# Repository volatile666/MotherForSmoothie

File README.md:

# MotherForSmoothie

#####DEVELOPMENT IN PROGRESS! UNTESTED!

Motherboad for LPCxpresso1769 and Pololu DRV8825 or compatible for running the awesome smoothieware. If you do have a spare LPCxpresso (maybe from a smoothie on breadboard experiment?) and dont need all of smoothieboards features this is for you.

#####Feature differences with smoothie

-80*100mm, 2 layers

-up to 4 stepper driver modules onboad, connector for 1 additional external driver

-no digital current adjustment (pot on the stepper modules instead)

-micro USB instead of USB-B

-1 big mosfet (heated bed?)

-1 small mosfet (extruder?)

-1 small mosfet connected to 12V (fan?)

-ATX connector for power supply, no internal regulators

-fan monitoring (for a critical fan)

-flowmeter connector with monitoring (laser cooling pump?)

#####What needs to be done?

-double check the things not in red boxes

-produce a prototype!

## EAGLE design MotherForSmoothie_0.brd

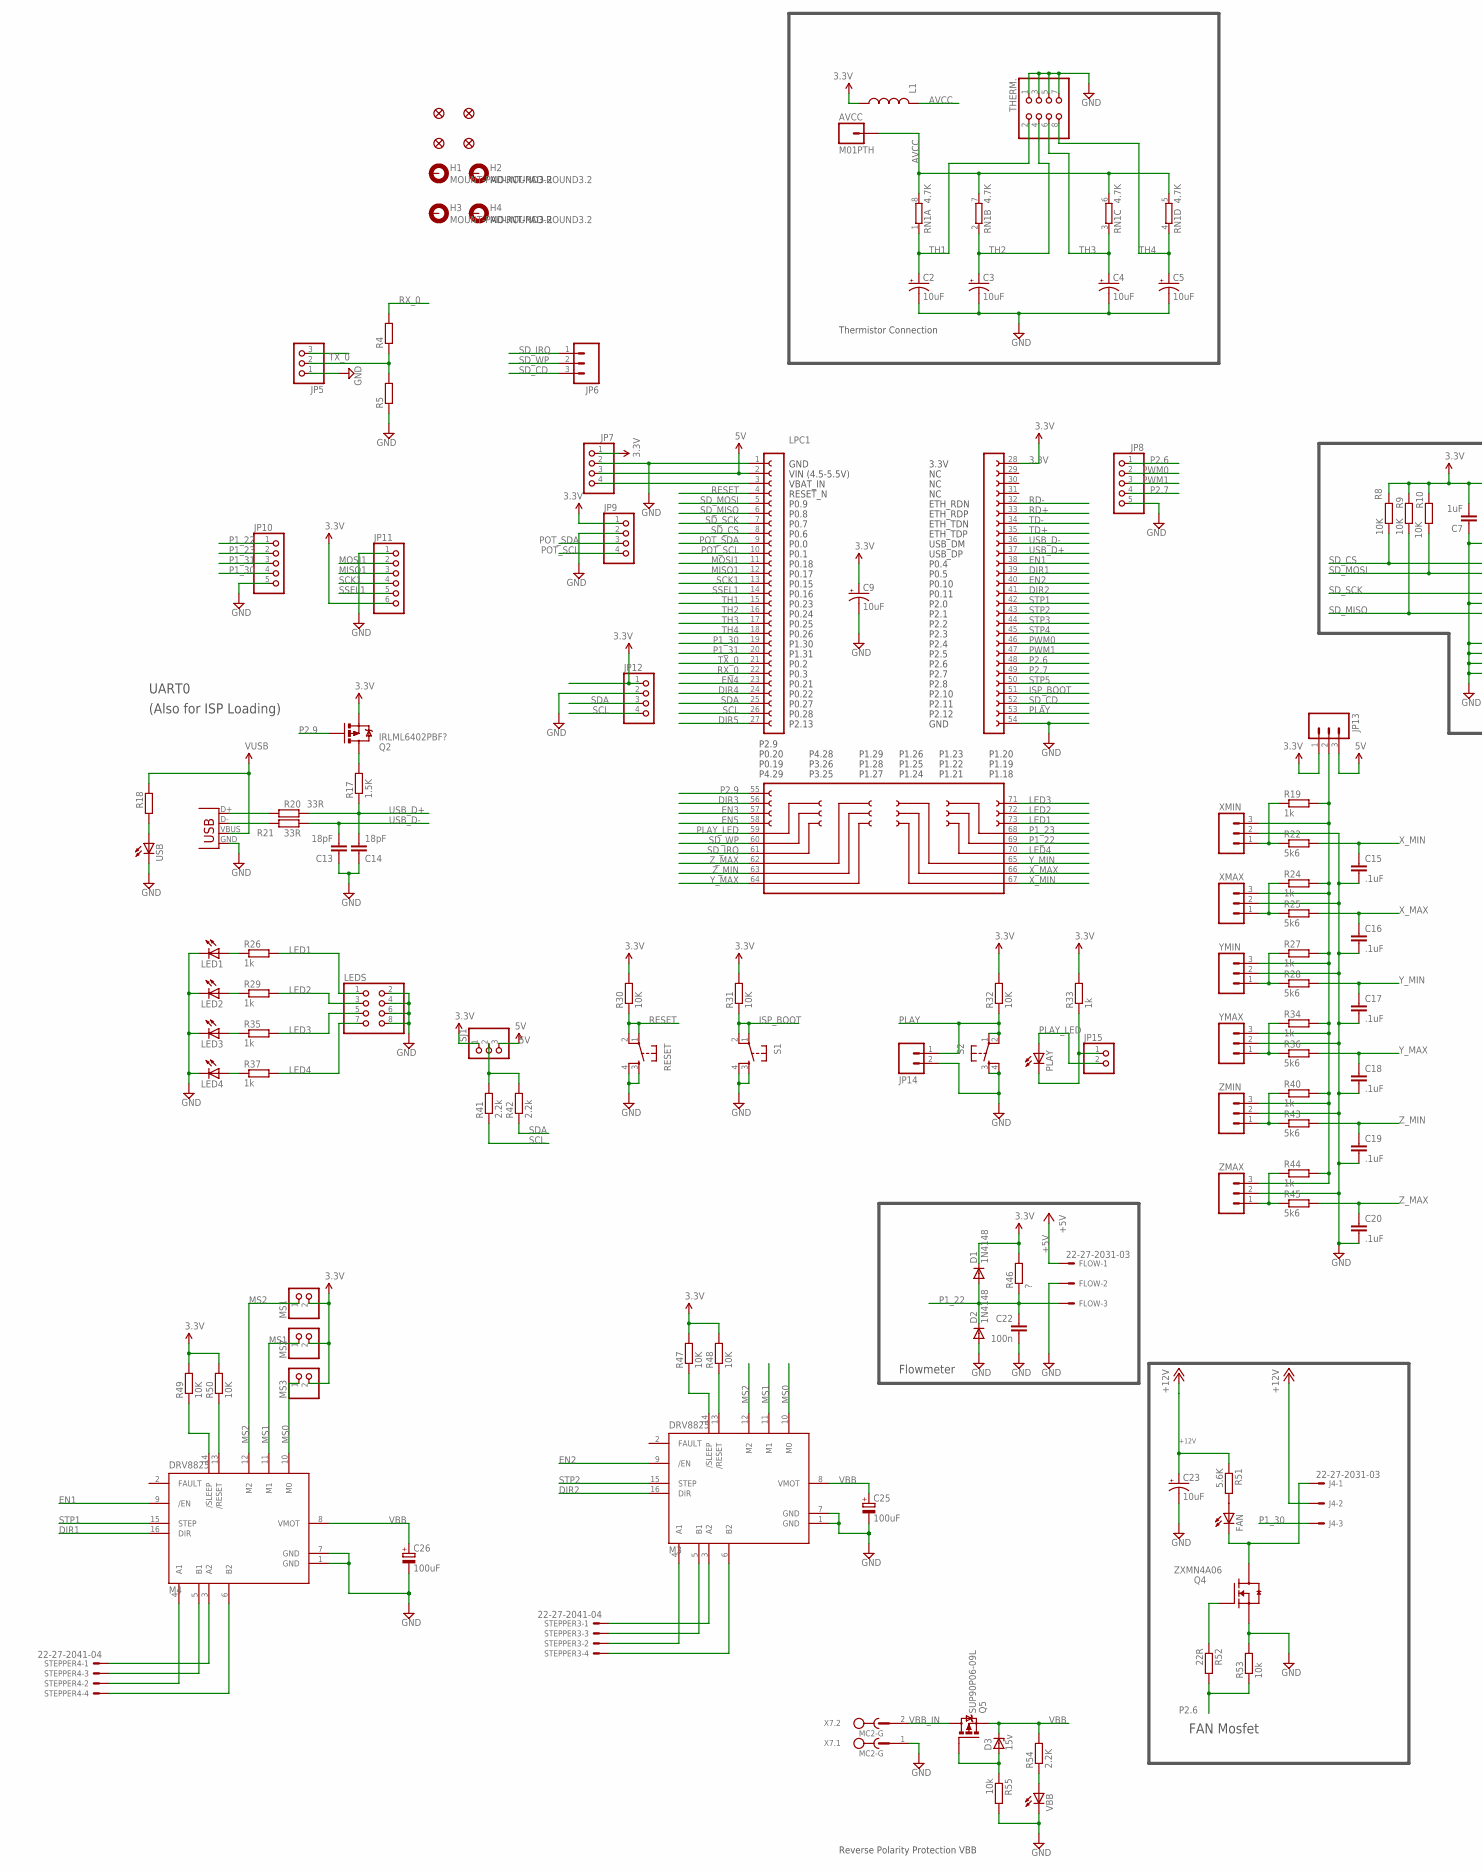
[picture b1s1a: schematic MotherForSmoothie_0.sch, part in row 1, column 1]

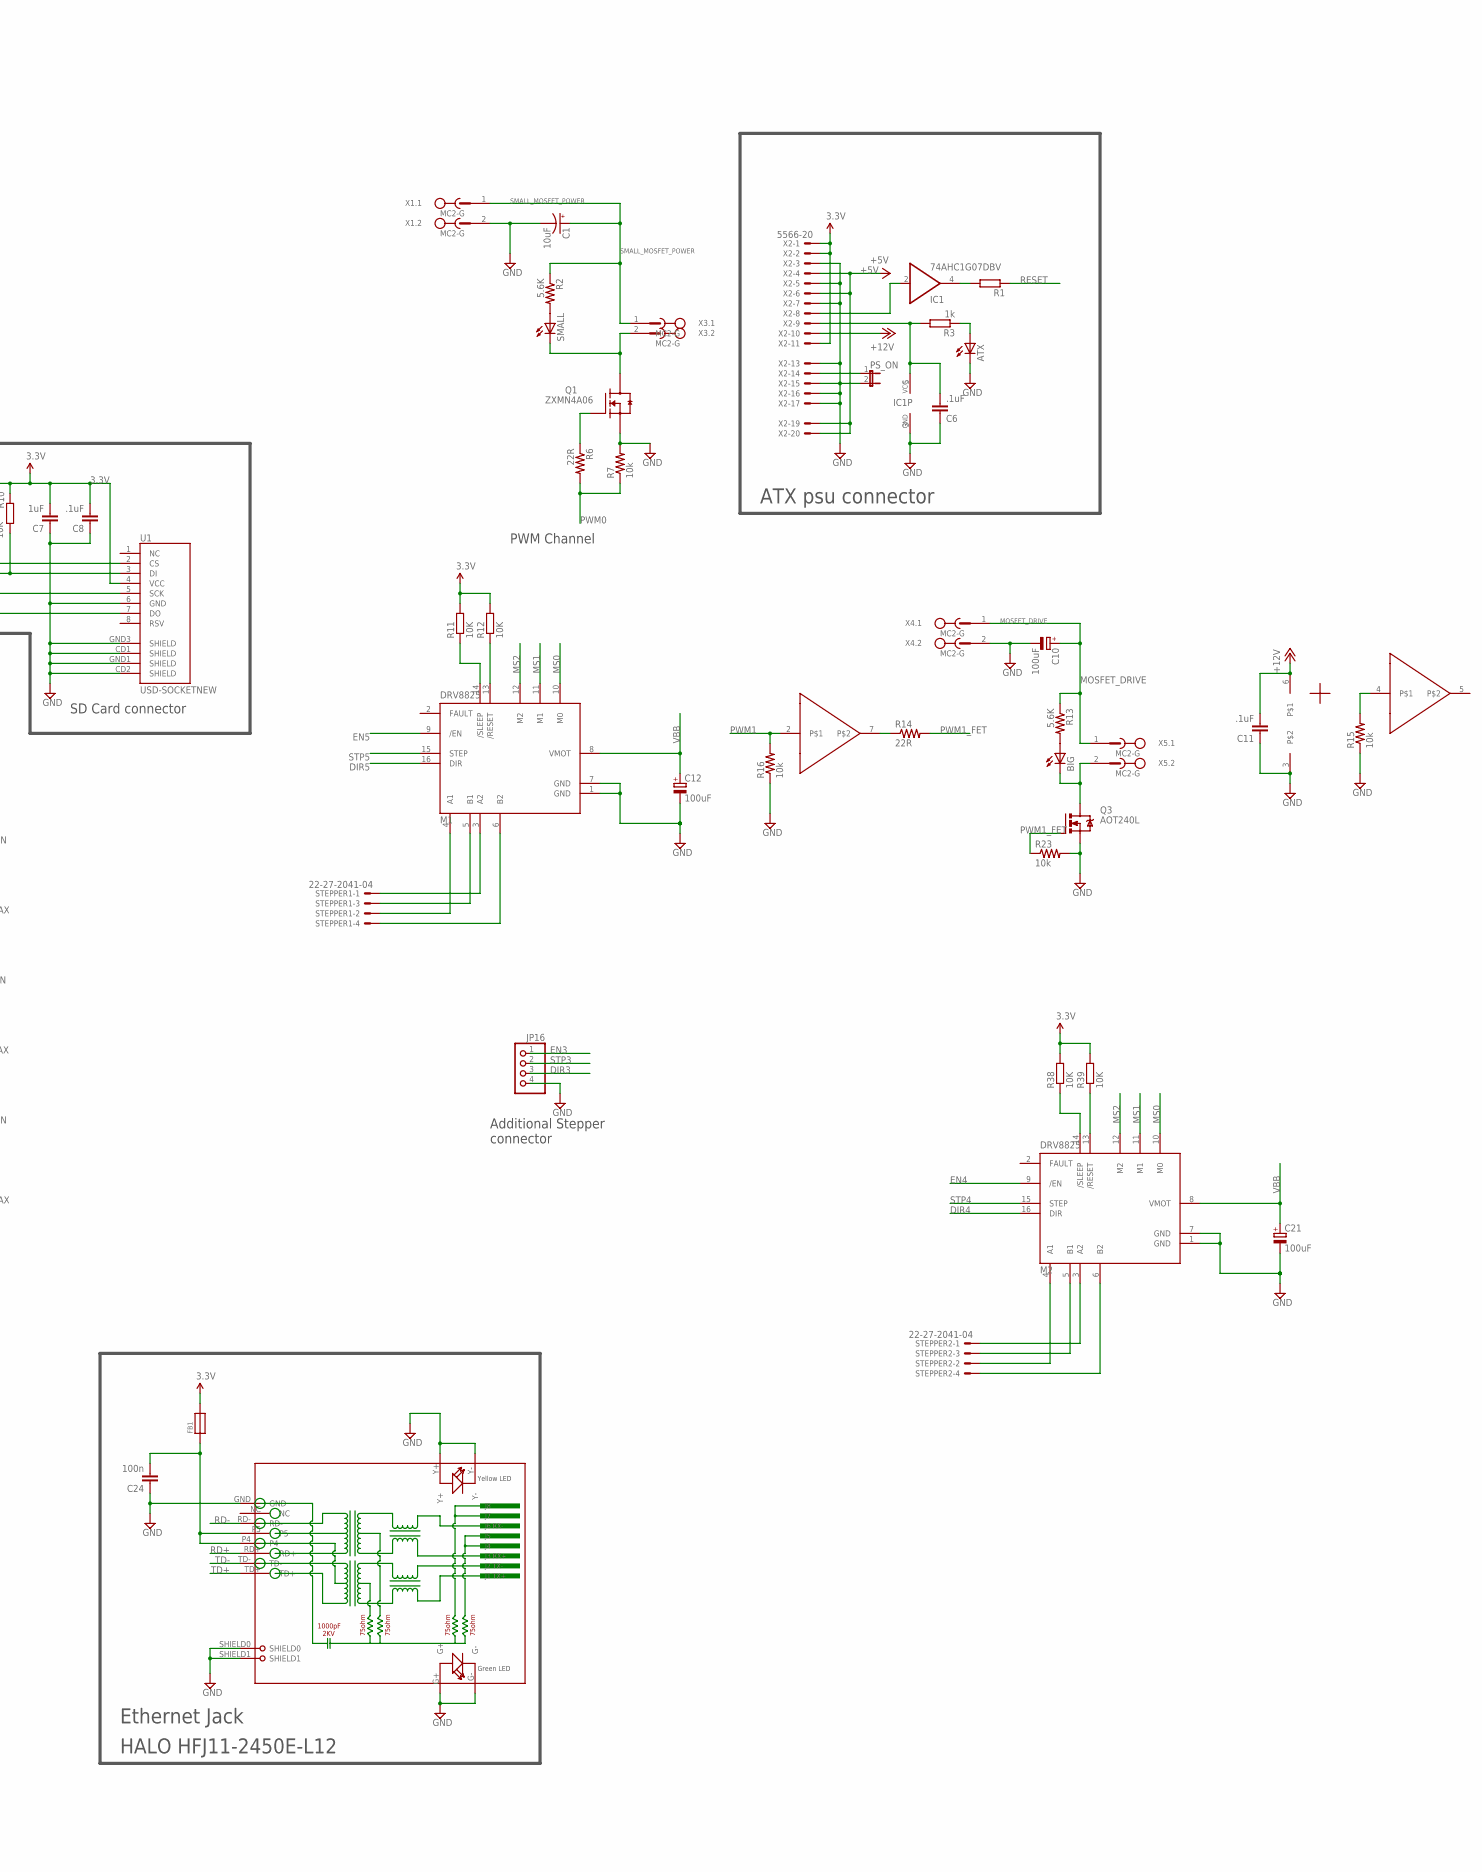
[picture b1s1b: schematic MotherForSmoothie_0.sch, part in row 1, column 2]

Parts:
ATX: LEDCHIPLED_0805; CHIPLED_0805
AVCC: M01PTH; 1X01
BIG: LEDCHIP-LED0805; CHIP-LED0805
C1, C2, C3, C4, C5, C23: 10uF; EIA3216
C6, C8, C11, C15, C16, C17, C18, C19, C20: .1uF; C0603
C7: 1uF; C0603
C9: 10uF; EIA6032
C10, C12, C21, C25, C26: 100uF; E5-8,5
C13, C14: 18pF; C0603
C22, C24: 100n; C0603
D1, D2: 1N4148; MINIMELF
D3: 15v; SMB
FAN: LEDCHIPLED_0805; CHIPLED_0805
FB1: FERRITE; 0603
FLOW: 22-27-2031-03; 6410-03
H1, H2, H3, H4: MOUNT-PAD-ROUND3.2; 3,2-PAD
IC1: 74AHC1G07DBV; SOT23-5
IC2: TC4427; SOIC8
J4: 22-27-2031-03; 6410-03
JP1, JP2, JP3, JP4: FIDUCIAL1X2; FIDUCIAL-1X2
JP5: PINHD-1X3_2.54-SMD; 1X03SMD
JP6, JP13: M031X03_NO_SILK; 1X03_NO_SILK
JP7, JP9, JP12, JP16: PINHD-1X4_2.54-SMD; 1X04SMD
JP8, JP10: PINHD-1X5_2.54-SMD; 1X05SMD
JP11: PINHD-1X6_2.54-SMD; 1X06SMD
JP14: M02PTH; 1X02
JP15: PINHD-1X2_2.54-SMD; 1X02SMD
L1: INDUCTOR0603; 0603
LED1, LED2, LED3, LED4: LEDCHIP-LED0805; CHIP-LED0805
LEDS: PINHD-2X4_2.54-SMD; 2X04SMD
LPC1: LPCXPRESSO_LPC1769SMD_PART; LPCXPRESSO_LPC1769_SMD
M1, M2, M3, M4: DRV8825
MS1, MS2, MS3: PINHD-1X2_2.54-SMD; 1X02SMD
PLAY: LEDCHIPLED_0805; CHIPLED_0805
PS_ON: JP1E; JP1
Q1, Q4: ZXMN4A06; SOT230P700X160-4N
Q2: IRLML6402PBF?; SOT23-3
Q3: AOT240L; TO220BV
Q5: SUP90P06-09L; TO220BV
R1, R4, R5, R18: R-EU_R0603; R0603
R2, R13, R51: 5.6K; R0603
R3, R19, R24, R26, R27, R29, R33, R34, R35, R37, R40, R44: 1k; R0603
R6, R14, R52: 22R; R0603
R7, R15, R16, R23, R53, R55: 10k; R0603
R8, R9, R10, R11, R12, R30, R31, R32, R38, R39, R47, R48, R49, R50: 10K; R0603
R17: 1.5K; R0603
R20, R21: 33R; R0603
R22, R25, R28, R36, R43, R45: 5k6; R0603
R41, R42: 2.2k; R0603
R46: ?; R0603
R54: 2.2K; R0603
RESET: TAC_SWITCHSMD; TACTILE_SWITCH_SMD
RJ1: HR911105A
RN1: 4.7K; 0603-ARV
S1, S2: TAC_SWITCHSMD; TACTILE_SWITCH_SMD
SJ1: PINHD-1X3_2.54-SMD; 1X03SMD
SMALL: LEDCHIP-LED0805; CHIP-LED0805
STEPPER1, STEPPER2, STEPPER3, STEPPER4: 22-27-2041-04; 6410-04
THERM.: PINHD-2X4MICROMATCH-SMD; SMDTOP8
U1: USD-SOCKETNEW; MICRO-SD-SOCKET-PP
USB: LEDCHIPLED_0805; CHIPLED_0805
VBB: LEDCHIPLED_0805; CHIPLED_0805
X1, X3, X4, X5, X7: MC2-G
X2: 5566-20
X6: USB-MICROB
XMAX: M031X03_NO_SILK; 1X03_NO_SILK
XMIN: M031X03_NO_SILK; 1X03_NO_SILK
YMAX: M031X03_NO_SILK; 1X03_NO_SILK
YMIN: M031X03_NO_SILK; 1X03_NO_SILK
ZMAX: M031X03_NO_SILK; 1X03_NO_SILK
ZMIN: M031X03_NO_SILK; 1X03_NO_SILK

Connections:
3.3V: C7.2, C8.2, C9.P$1 (+), D1.C, FB1.2, JP7.1, JP9.1, JP11.6, JP12.1, JP13.1, L1.2, LPC1.28, MS1.2, MS2.2, MS3.2, Q2.2 (S), R8.2, R9.2, R10.2, R11.2, R12.2, R30.2, R31.2, R32.2, R33.2, R38.2, R39.2, R46.2, R47.2, R48.2, R49.2, R50.2, SJ1.1, U1.4 (VCC), X2.1, X2.2, X2.11
5V: JP7.3, JP13.3, LPC1.2, SJ1.3
+5V: FLOW.1, X2.4, X2.6, X2.19, X2.20
+12V: C11.2, C23.A (+), IC2.6, J4.2, R51.1, X2.10
AVCC: AVCC.1, L1.1, RN1.5 (2), RN1.6 (2), RN1.7 (2), RN1.8 (2)
DIR1: LPC1.39, M4.16 (DIR)
DIR2: LPC1.41, M3.16 (DIR)
DIR3: JP16.3, LPC1.56
DIR4: LPC1.24, M2.16 (DIR)
DIR5: LPC1.27, M1.16 (DIR)
EN1: LPC1.38, M4.9 (/EN)
EN2: LPC1.40, M3.9 (/EN)
EN3: JP16.1, LPC1.57
EN4: LPC1.23, M2.9 (/EN)
EN5: LPC1.58, M1.9 (/EN)
GND: ATX.C, C1.C (-), C2.C (-), C3.C (-), C4.C (-), C5.C (-), C6.1, C7.1, C8.1, C9.P$2 (-), C10.-, C11.1, C12.-, C13.1, C14.1, C15.2, C16.2, C17.2, C18.2, C19.2, C20.2, C21.-, C22.2, C23.C (-), C24.1, C25.-, C26.-, D2.A, FLOW.2, IC1.3 (GND), IC2.3, JP5.1, JP7.2, JP8.5, JP9.2, JP10.5, JP11.1, JP12.2, JP14.2, JP16.4, LED1.C, LED2.C, LED3.C, LED4.C, LEDS.2, LEDS.4, LEDS.6, LEDS.8, LPC1.1, LPC1.54, M1.1 (GND), M1.7 (GND), M2.1 (GND), M2.7 (GND), M3.1 (GND), M3.7 (GND), M4.1 (GND), M4.7 (GND), PS_ON.2, Q1.3 (S), Q3.S, Q4.3 (S), R5.1, R7.2, R15.1, R16.1, R23.2, R53.2, R55.2, RESET.3, RESET.4, RJ1.G+, RJ1.G-, RJ1.GND, RJ1.SHIELD0, RJ1.SHIELD1, RJ1.Y+, RJ1.Y-, S1.3, S1.4, S2.3, S2.4, THERM..1, THERM..3, THERM..5, THERM..7, U1.6 (GND), U1.CD1 (SHIELD), U1.CD2 (SHIELD), U1.GND1 (SHIELD), U1.GND3 (SHIELD), USB.C, VBB.C, X1.2, X2.3, X2.5, X2.7, X2.13, X2.15, X2.16, X2.17, X4.2, X6.GND, X7.1, XMAX.2, XMIN.2, YMAX.2, YMIN.2, ZMAX.2, ZMIN.2
ISP_BOOT: LPC1.51, R31.1, S1.1, S1.2
LED1: LEDS.1, LPC1.73, R26.2
LED2: LEDS.3, LPC1.72, R29.2
LED3: LEDS.5, LPC1.71, R35.2
LED4: LEDS.7, LPC1.70, R37.2
MISO1: JP11.3, LPC1.12
MOSFET_DRIVE: C10.+, R13.1, X4.1, X5.1
MOSI1: JP11.2, LPC1.11
MS0: M1.10 (M0), M2.10 (M0), M3.10 (M0), M4.10 (M0), MS3.1
MS1: M1.11 (M1), M2.11 (M1), M3.11 (M1), M4.11 (M1), MS2.1
MS2: M1.12 (M2), M2.12 (M2), M3.12 (M2), M4.12 (M2), MS1.1
unnamed: R20.1, X6.D+
unnamed: R21.1, X6.D-
unnamed: M4.5 (B1), STEPPER4.3
unnamed: M4.6 (B2), STEPPER4.4
unnamed: LED4.A, R37.1
unnamed: LED3.A, R35.1
unnamed: LED2.A, R29.1
unnamed: M4.4 (A1), STEPPER4.2
unnamed: M4.3 (A2), STEPPER4.1
unnamed: LED1.A, R26.1
unnamed: M2.5 (B1), STEPPER2.3
unnamed: Q2.3 (D), R17.2
unnamed: M2.6 (B2), STEPPER2.4
unnamed: JP13.2, R19.2, R24.2, R27.2, R34.2, R40.2, R44.2, XMAX.3, XMIN.3, YMAX.3, YMIN.3, ZMAX.3, ZMIN.3
unnamed: R40.1, R43.1, ZMIN.1
unnamed: R19.1, R22.1, XMIN.1
unnamed: M4.14 (/SLEEP), R49.1
unnamed: R24.1, R25.1, XMAX.1
unnamed: R27.1, R28.1, YMIN.1
unnamed: R34.1, R36.1, YMAX.1
unnamed: M2.4 (A1), STEPPER2.2
unnamed: M3.5 (B1), STEPPER3.3
unnamed: JP7.4, LPC1.3
unnamed: R44.1, R45.1, ZMAX.1
unnamed: M3.6 (B2), STEPPER3.4
unnamed: M3.4 (A1), STEPPER3.2
unnamed: R41.2, R42.2, SJ1.2
unnamed: M3.3 (A2), STEPPER3.1
unnamed: M3.14 (/SLEEP), R47.1
unnamed: M2.3 (A2), STEPPER2.1
unnamed: M2.14 (/SLEEP), R38.1
unnamed: M2.13 (/RESET), R39.1
unnamed: C6.2, IC1.5 (VCC), R3.2, X2.9
unnamed: IC1.2 (I), X2.8
unnamed: ATX.A, R3.1
unnamed: PS_ON.1, X2.14
unnamed: JP5.2, R4.1, R5.2
unnamed: IC1.4 (O), R1.2
unnamed: IC2.7, R14.1
unnamed: R18.1, USB.A
unnamed: M4.13 (/RESET), R50.1
unnamed: M3.13 (/RESET), R48.1
unnamed: Q1.1 (G), R6.1
unnamed: R2.2, SMALL.A
unnamed: Q1.4 (D), SMALL.C, X3.2
unnamed: BIG.C, Q3.D, X5.2
unnamed: FAN.C, J4.1, Q4.4 (D)
unnamed: BIG.A, R13.2
unnamed: Q4.1 (G), R52.1
unnamed: R54.1, VBB.A
unnamed: FAN.A, R51.2
unnamed: D3.A, Q5.G, R55.1
unnamed: C24.2, FB1.1, RJ1.P4, RJ1.P5
unnamed: M1.5 (B1), STEPPER1.3
unnamed: M1.6 (B2), STEPPER1.4
unnamed: M1.4 (A1), STEPPER1.2
unnamed: M1.3 (A2), STEPPER1.1
unnamed: M1.14 (/SLEEP), R11.1
unnamed: M1.13 (/RESET), R12.1
unnamed: JP15.1, PLAY.C, R33.1
P1_22: C22.1, D1.A, D2.C, FLOW.3, JP10.1, LPC1.69, R46.1
P1_23: JP10.2, LPC1.68
P1_30: J4.3, JP10.4, LPC1.19
P1_31: JP10.3, LPC1.20
P2.6: JP8.1, LPC1.48, R52.2, R53.1
P2.7: JP8.4, LPC1.49
P2.9: LPC1.55, Q2.1 (G)
PLAY: JP14.1, LPC1.53, R32.1, S2.1, S2.2
PLAY_LED: JP15.2, LPC1.59, PLAY.A
POT_SCL: JP9.4, LPC1.10
POT_SDA: JP9.3, LPC1.9
PWM0: JP8.2, LPC1.46, R6.2, R7.1
PWM1: IC2.2, JP8.3, LPC1.47, R16.2
PWM1_FET: Q3.G, R14.2, R23.1
RD+: LPC1.33, RJ1.RD+
RD-: LPC1.32, RJ1.RD-
RESET: LPC1.4, R1.1, R30.1, RESET.1, RESET.2
RX_0: LPC1.22, R4.2
SCK1: JP11.4, LPC1.13
SCL: JP12.4, LPC1.26, R41.1
SDA: JP12.3, LPC1.25, R42.1
SD_CD: JP6.3, LPC1.52
SD_CS: LPC1.8, R8.1, U1.2 (CS)
SD_IRQ: JP6.1, LPC1.61
SD_MISO: LPC1.6, R9.1, U1.7 (DO)
SD_MOSI: LPC1.5, R10.1, U1.3 (DI)
SD_SCK: LPC1.7, U1.5 (SCK)
SD_WP: JP6.2, LPC1.60
SMALL_MOSFET_POWER: C1.A (+), R2.1, X1.1, X3.1
SSDFGSDFG: IC2.4, R15.2
SSEL1: JP11.5, LPC1.14
STP1: LPC1.42, M4.15 (STEP)
STP2: LPC1.43, M3.15 (STEP)
STP3: JP16.2, LPC1.44
STP4: LPC1.45, M2.15 (STEP)
STP5: LPC1.50, M1.15 (STEP)
TD+: LPC1.35, RJ1.TD+
TD-: LPC1.34, RJ1.TD-
TH1: C2.A (+), LPC1.15, RN1.1, THERM..2
TH2: C3.A (+), LPC1.16, RN1.2 (1), THERM..4
TH3: C4.A (+), LPC1.17, RN1.3 (1), THERM..6
TH4: C5.A (+), LPC1.18, RN1.4 (1), THERM..8
TX_0: JP5.3, LPC1.21
USB_D+: C14.2, LPC1.37, R17.1, R20.2
USB_D-: C13.2, LPC1.36, R21.2
VBB: C12.+, C21.+, C25.+, C26.+, D3.C, M1.8 (VMOT), M2.8 (VMOT), M3.8 (VMOT), M4.8 (VMOT), Q5.S, R54.2
VBB_IN: Q5.D, X7.2
VUSB: R18.2, X6.VBUS
X_MAX: C16.1, LPC1.66, R25.2
X_MIN: C15.1, LPC1.67, R22.2
Y_MAX: C18.1, LPC1.64, R36.2
Y_MIN: C17.1, LPC1.65, R28.2
Z_MAX: C20.1, LPC1.62, R45.2
Z_MIN: C19.1, LPC1.63, R43.2

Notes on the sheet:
FAN Mosfet
SD Card connector
UART0
(Also for ISP Loading)
PWM Channel
Thermistor Connection
Flowmeter
Reverse Polarity Protection VBB
Ethernet Jack
HALO HFJ11-2450E-L12
ATX psu connector
Additional Stepper connector

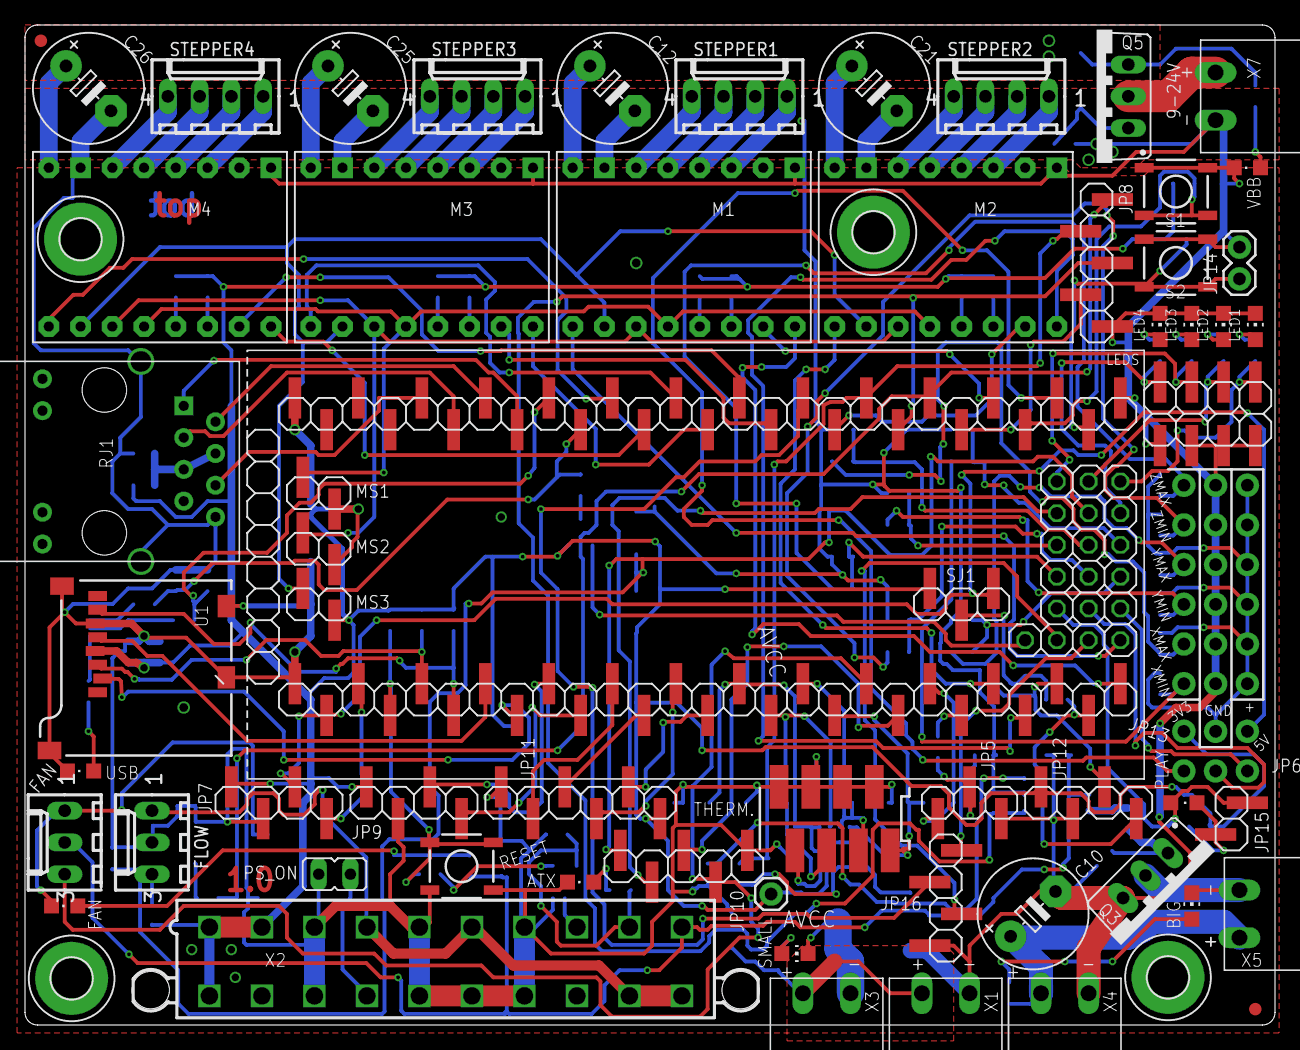
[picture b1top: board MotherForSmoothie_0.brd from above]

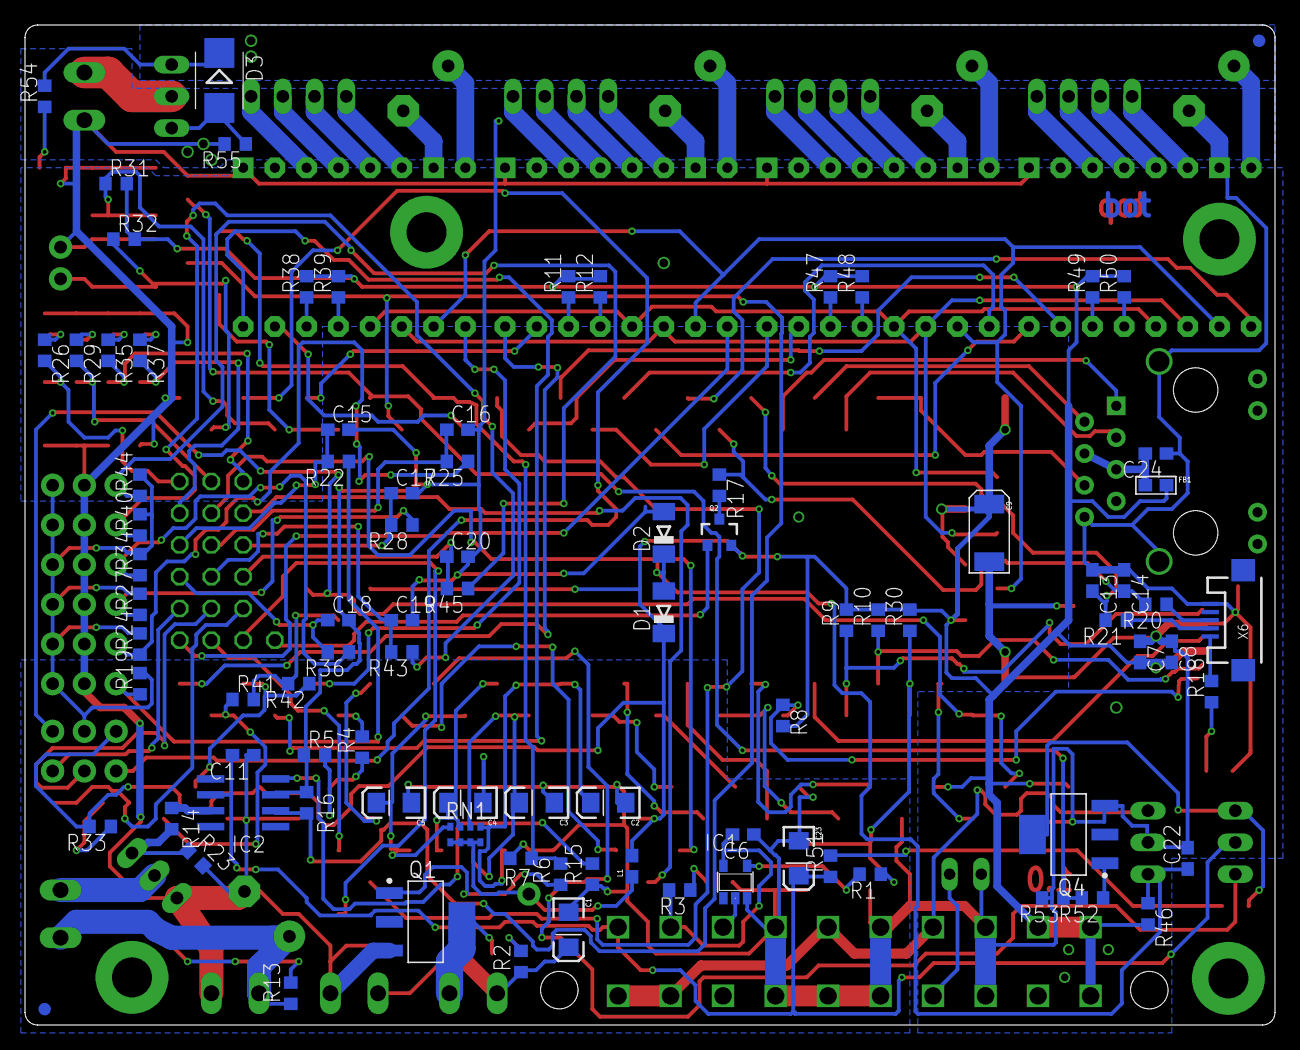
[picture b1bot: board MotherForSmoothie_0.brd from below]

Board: 2 copper layers, 100.0 x 80.0 mm, 162 parts (90 on the bottom side), 141 nets.

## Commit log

2015-01-24 Preliminary placement
2015-01-25 100% routed, still preliminary
2015-01-25 Eagle Files
2015-01-26 Updated board and schematic
2015-01-27 More cleanup and fixes
2015-02-16 Mostly checked
2015-03-14 More cleanup done
